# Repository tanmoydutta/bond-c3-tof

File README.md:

# bond-c3-tof
A time of flight sensor integrated with ESP32-C3

It also has a matching 3D printed box to house the circuit along with an option to stick a 12x3mm neodymium magnet to stick this to a metallic surface

This project is certified as Open Source Hardware - 
<p align="center">
  
</p>

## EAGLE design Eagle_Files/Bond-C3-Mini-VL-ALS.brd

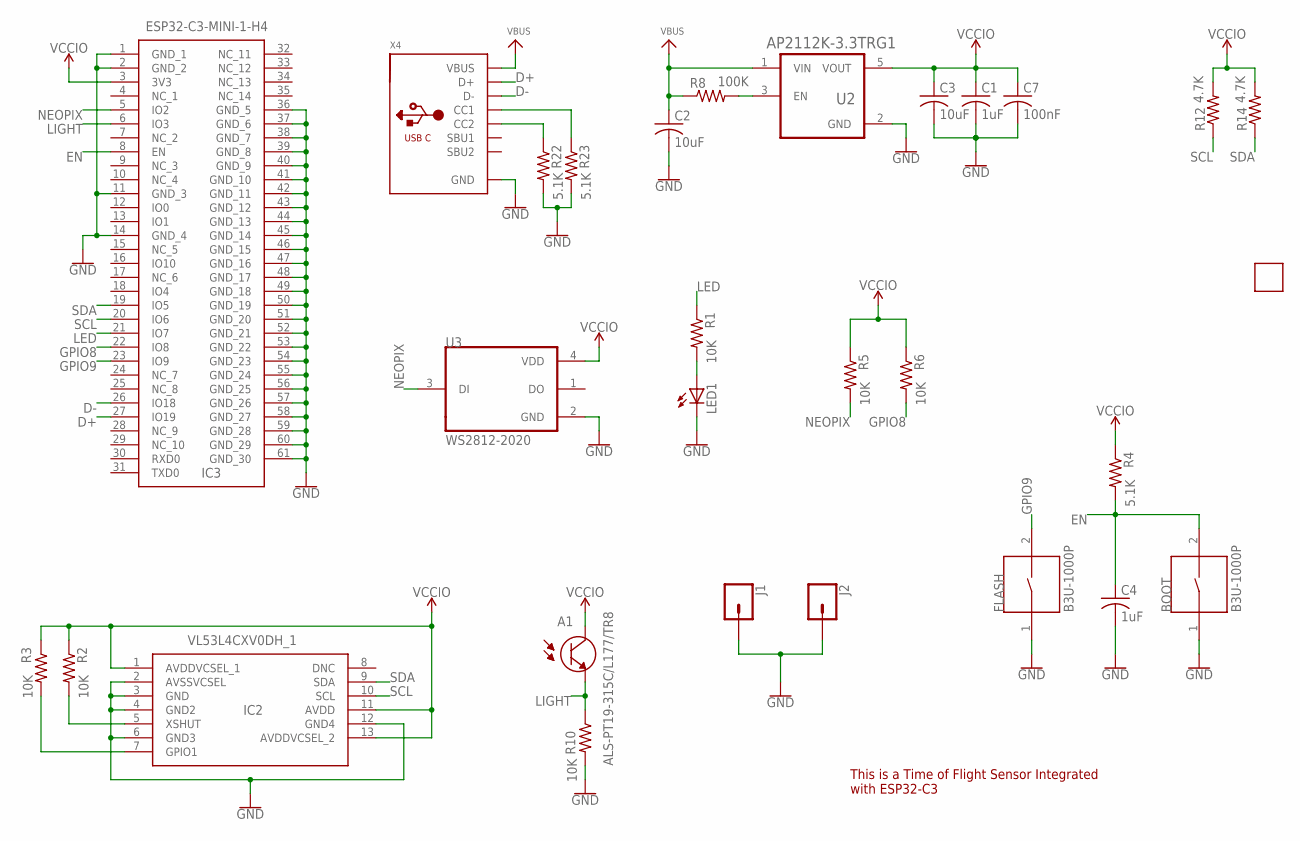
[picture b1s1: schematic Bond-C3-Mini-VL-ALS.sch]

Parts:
A1: ALS-PT19-315C/L177/TR8; XDCR_ALS-PT19-315C/L177/TR8
BOOT: B3U-1000P; SW_B3U-1000P
C1, C4: 1uF; C0402
C2, C3: 10uF; C0402
C7: 100nF; C0402
FLASH: B3U-1000P; SW_B3U-1000P
IC2: VL53L4CXV0DH_1; VL53L4CXV0DH1
IC3: ESP32-C3-MINI-1-H4; ESP32C3MINI1H4
J1, J2: CONN_01PTH_2MM; 1X01_2MM
LED1: LEDCHIP-LED0603; CHIP-LED0603
R1, R2, R3, R5, R6, R10: 10K; R0402
R4, R22, R23: 5.1K; R0402
R8: 100K; R0402
R12, R14: 4.7K; R0402
U2: AP2112K-3.3TRG1; SOT95P285X140-5N
U3: WS2812-2020; LED_WS2812-2020
U$1: SMARTT_SMALL
X4: MICROBUILDER_USB_C; MICROBUILDER_USB_C_CUSB31-CFM2AX-01-X

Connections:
D+: IC3.27 (IO19), X4.A6 (D+), X4.B6 (D+)
D-: IC3.26 (IO18), X4.A7 (D-), X4.B7 (D-)
EN: BOOT.2, C4.1, IC3.8 (EN), R4.2
GND: BOOT.1, C1.2, C2.2, C3.2, C4.2, C7.2, FLASH.1, IC2.2 (AVSSVCSEL), IC2.3 (GND), IC2.4 (GND2), IC2.6 (GND3), IC2.12 (GND4), IC3.1 (GND_1), IC3.2 (GND_2), IC3.11 (GND_3), IC3.14 (GND_4), IC3.36 (GND_5), IC3.37 (GND_6), IC3.38 (GND_7), IC3.39 (GND_8), IC3.40 (GND_9), IC3.41 (GND_10), IC3.42 (GND_11), IC3.43 (GND_12), IC3.44 (GND_13), IC3.45 (GND_14), IC3.46 (GND_15), IC3.47 (GND_16), IC3.48 (GND_17), IC3.49 (GND_18), IC3.50 (GND_19), IC3.51 (GND_20), IC3.52 (GND_21), IC3.53 (GND_22), IC3.54 (GND_23), IC3.55 (GND_24), IC3.56 (GND_25), IC3.57 (GND_26), IC3.58 (GND_27), IC3.59 (GND_28), IC3.60 (GND_29), IC3.61 (GND_30), J1.1, J2.1, LED1.C, R10.2, R22.2, R23.2, U2.2 (GND), U3.2 (GND), X4.A1B12 (GND), X4.B1A12 (GND)
GPIO8: IC3.22 (IO8), R6.2
GPIO9: FLASH.2, IC3.23 (IO9)
LED: IC3.21 (IO7), R1.1
LIGHT: A1.2 (E), IC3.6 (IO3), R10.1
unnamed: IC2.7 (GPIO1), R3.2
unnamed: IC2.5 (XSHUT), R2.2
unnamed: LED1.A, R1.2
unnamed: R22.1, X4.B5 (CC2)
unnamed: R23.1, X4.A5 (CC1)
unnamed: R8.2, U2.3 (EN)
NEOPIX: IC3.5 (IO2), R5.2, U3.3 (DI)
SCL: IC2.10 (SCL), IC3.20 (IO6), R12.1
SDA: IC2.9 (SDA), IC3.19 (IO5), R14.1
VBUS: C2.1, R8.1, U2.1 (VIN), X4.A4B9 (VBUS), X4.B4A9 (VBUS)
VCCIO: A1.1 (C), C1.1, C3.1, C7.1, IC2.1 (AVDDVCSEL_1), IC2.11 (AVDD), IC2.13 (AVDDVCSEL_2), IC3.3 (3V3), R2.1, R3.1, R4.1, R5.1, R6.1, R12.2, R14.2, U2.5 (VOUT), U3.4 (VDD)

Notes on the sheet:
This is a Time of Flight Sensor Integrated with ESP32-C3

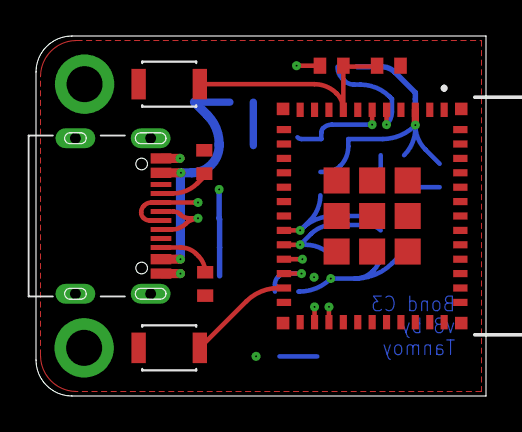
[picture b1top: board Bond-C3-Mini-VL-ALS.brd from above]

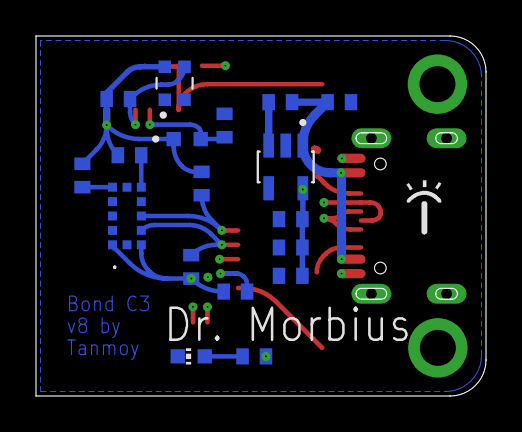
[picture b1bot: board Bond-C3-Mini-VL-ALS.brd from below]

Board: 4 copper layers, 25.0 x 20.0 mm, 29 parts (18 on the bottom side), 19 nets.

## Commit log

2026-05-14 Adding files and images
2026-05-14 Adding images and documentation
2026-05-20 Adding OSHWA mark
2026-05-21 Readme update

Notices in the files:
parts and their libraries:
SparkFun-Connectors: Licensing: Creative Commons ShareAlike 4.0 International - https://creativecommons.org/licenses/by-sa/4.0
